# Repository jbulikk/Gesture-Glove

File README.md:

# Gesture Glove
The purpose of this project is to design and implement a prototype glove for gesture-based computer control, equipped with a set of sensors and a microcontroller. 

The project integrates flex sensors that measure finger bending and an inertial module containing an accelerometer and gyroscope, enabling gesture recognition based on spatial orientation. A key system component is the decision unit, which analyses sensor data and compares it with predefined patterns. Recognized
gestures are then transmitted to the computer via a USB HID interface.

The designed PCB, measuring 47.5 mm by 54.5 mm, was created to optimize the system's dimensions and facilitate durable mounting on the glove.
The results include successful recognition gestures and seamless
integration with the computer via USB HID. 

Future development plans involve further PCB miniaturization using a dedicated integrated circuit, the introduction of a wireless communication interface, and the design of a battery-powered system. Additionally, optimization of the decision algorithm is planned to improve gesture recognition accuracy.

# Overview

🎥 [Demo 1](https://youtube.com/shorts/HhJ9UxrMhsA?si=5mQ5Ls-5uZ076j6t)
🎥 [Demo 2](https://youtube.com/shorts/HhJ9UxrMhsA?si=OoEMOWHLwrecI-b9)

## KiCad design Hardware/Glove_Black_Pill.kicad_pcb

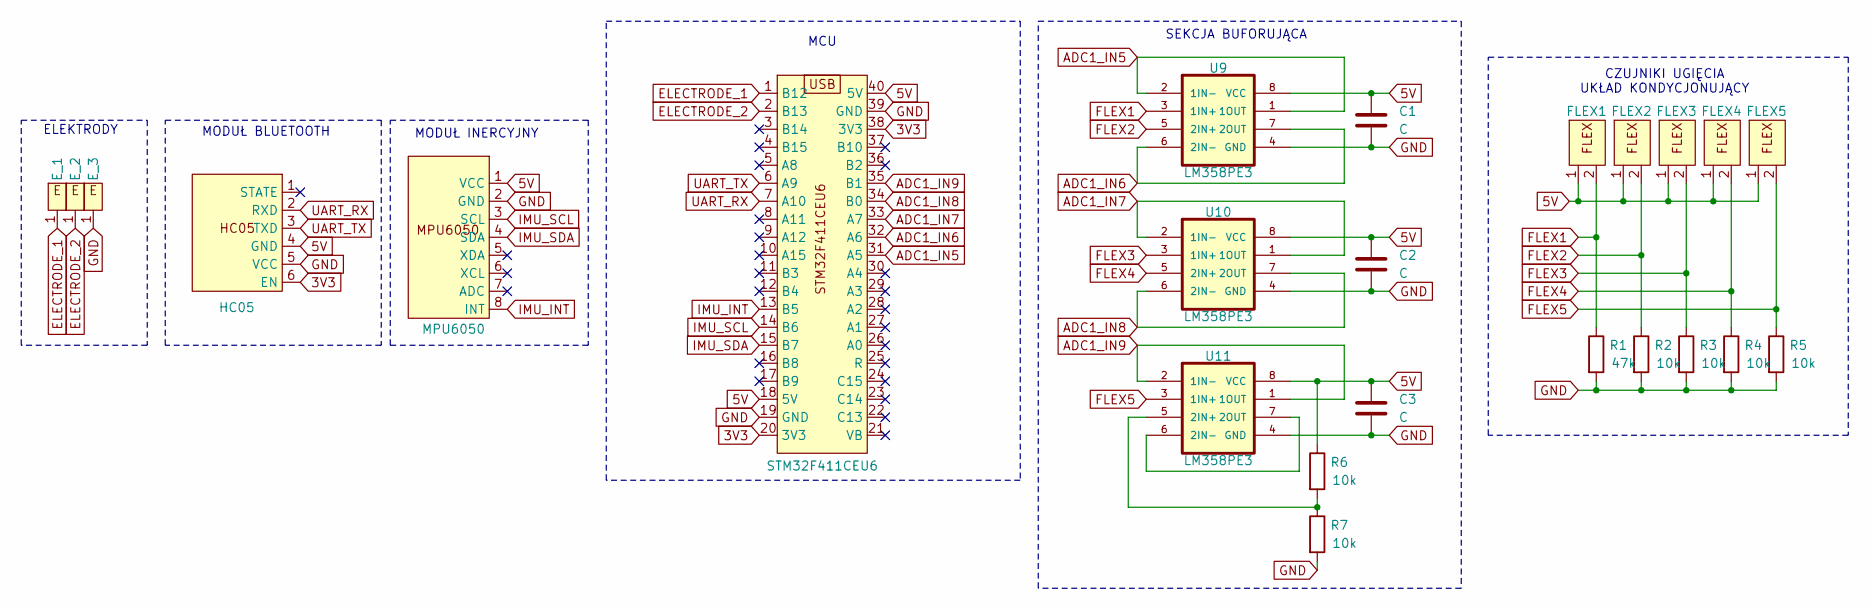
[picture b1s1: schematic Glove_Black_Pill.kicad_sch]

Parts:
C1, C2, C3: C; R_0805_2012Metric_Pad1.20x1.40mm_HandSolder
E_1, E_2, E_3: TestPoint_Loop_D2.50mm_Drill1.0mm
FLEX1, FLEX2, FLEX3, FLEX4, FLEX5: FLEX
HC05: HC-05
MPU6050: MPU6050
R1: 47k; R_0805_2012Metric_Pad1.20x1.40mm_HandSolder
R2, R3, R4, R5, R6, R7: 10k; R_0805_2012Metric_Pad1.20x1.40mm_HandSolder
STM32F411CEU6: STM32F411CEU6
U9, U10, U11: LM358PE3; DIP794W45P254L959H508Q8

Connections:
3V3: HC05.6 (EN), STM32F411CEU6.20 (3V3), STM32F411CEU6.38 (3V3)
5V: C1.1, C2.1, C3.1, FLEX1.1, FLEX2.1, FLEX3.1, FLEX4.1, FLEX5.1, HC05.4 (GND), MPU6050.1 (VCC), R6.1, STM32F411CEU6.18 (5V), STM32F411CEU6.40 (5V), U9.8 (VCC), U10.8 (VCC), U11.8 (VCC); also elsewhere on the board
ADC1_IN5: STM32F411CEU6.31 (A5), U9.1 (1OUT), U9.2 (1IN-)
ADC1_IN6: STM32F411CEU6.32 (A6), U9.6 (2IN-), U9.7 (2OUT)
ADC1_IN7: STM32F411CEU6.33 (A7), U10.1 (1OUT), U10.2 (1IN-)
ADC1_IN8: STM32F411CEU6.34 (B0), U10.6 (2IN-), U10.7 (2OUT)
ADC1_IN9: STM32F411CEU6.35 (B1), U11.1 (1OUT), U11.2 (1IN-)
ELECTRODE_1: E_1.1, STM32F411CEU6.1 (B12)
ELECTRODE_2: E_2.1, STM32F411CEU6.2 (B13)
FLEX1: FLEX1.2, R1.1, U9.3 (1IN+); also elsewhere on the board
FLEX2: FLEX2.2, R2.1, U9.5 (2IN+)
FLEX3: FLEX3.2, R3.1, U10.3 (1IN+)
FLEX4: FLEX4.2, R4.1, U10.5 (2IN+)
FLEX5: FLEX5.2, R5.1, U11.3 (1IN+)
GND: C1.2, C2.2, C3.2, E_3.1, HC05.5 (VCC), MPU6050.2 (GND), R1.2, R2.2, R3.2, R4.2, R5.2, R7.2, STM32F411CEU6.19 (GND), STM32F411CEU6.39 (GND), U9.4 (GND), U10.4 (GND), U11.4 (GND)
IMU_INT: MPU6050.8 (INT), STM32F411CEU6.13 (B5)
IMU_SCL: MPU6050.3 (SCL), STM32F411CEU6.14 (B6)
IMU_SDA: MPU6050.4 (SDA), STM32F411CEU6.15 (B7)
unnamed: R6.2, R7.1, U11.5 (2IN+)
unnamed: U11.6 (2IN-), U11.7 (2OUT)
UART_RX: HC05.2 (RXD), STM32F411CEU6.7 (A10)
UART_TX: HC05.3 (TXD), STM32F411CEU6.6 (A9)

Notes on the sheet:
MODUŁ BLUETOOTH
MODUŁ INERCYJNY
SEKCJA BUFORUJĄCA
ELEKTRODY
MCU
CZUJNIKI UGIĘCIA UKŁAD KONDYCJONUJĄCY

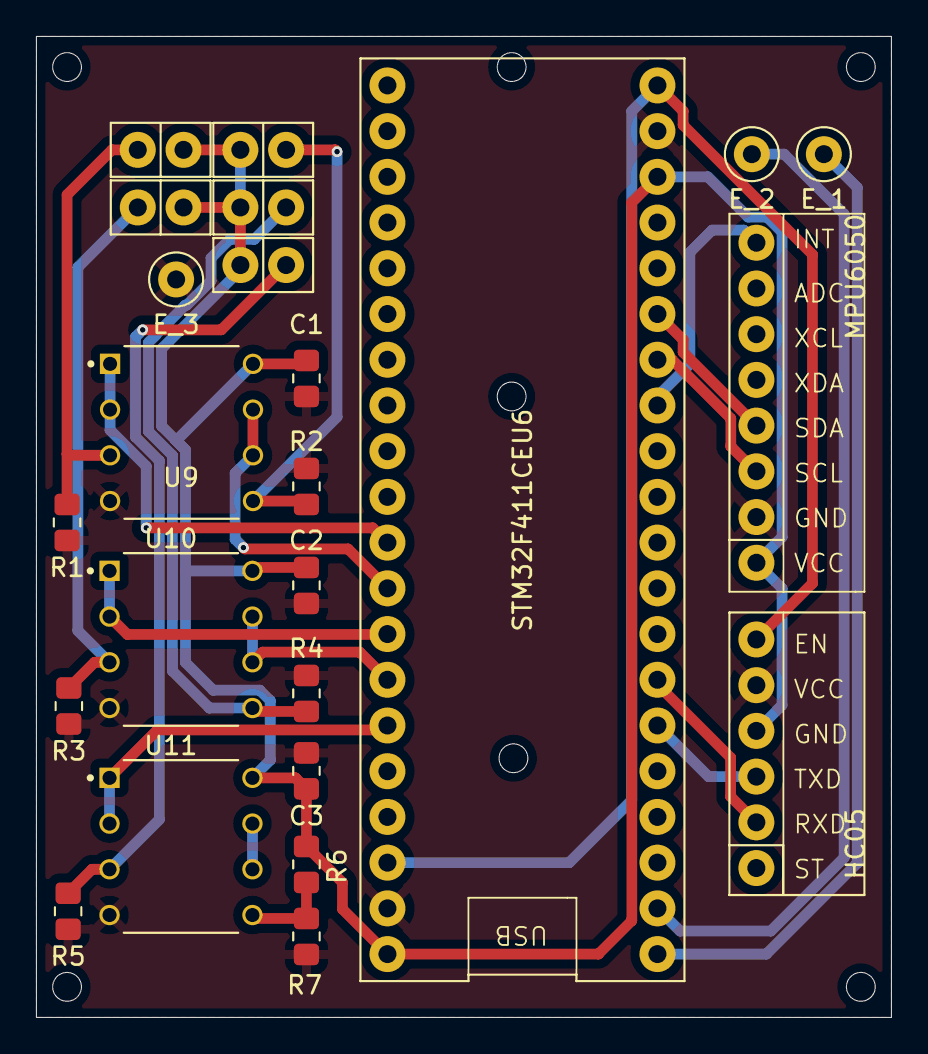
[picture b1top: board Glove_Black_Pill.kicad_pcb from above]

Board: 4 copper layers, 47.5 x 54.5 mm, 24 parts (0 on the bottom side), 22 nets.

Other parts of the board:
.: FLEX

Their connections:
5V: ..1; also elsewhere on the board
FLEX1: ..2; also elsewhere on the board

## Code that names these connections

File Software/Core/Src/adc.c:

/* USER CODE BEGIN Header */
/**
  ******************************************************************************
  * @file    adc.c
  * @brief   This file provides code for the configuration
  *          of the ADC instances.
  ******************************************************************************
  * @attention
  *
  * Copyright (c) 2024 STMicroelectronics.
  * All rights reserved.
  *
  * This software is licensed under terms that can be found in the LICENSE file
  * in the root directory of this software component.
  * If no LICENSE file comes with this software, it is provided AS-IS.
  *
  ******************************************************************************
  */
/* USER CODE END Header */
/* Includes ------------------------------------------------------------------*/
#include "adc.h"

/* USER CODE BEGIN 0 */

/* USER CODE END 0 */

ADC_HandleTypeDef hadc1;
DMA_HandleTypeDef hdma_adc1;

/* ADC1 init function */
void MX_ADC1_Init(void)
{

  /* USER CODE BEGIN ADC1_Init 0 */

  /* USER CODE END ADC1_Init 0 */

  ADC_ChannelConfTypeDef sConfig = {0};

  /* USER CODE BEGIN ADC1_Init 1 */

  /* USER CODE END ADC1_Init 1 */

  /** Configure the global features of the ADC (Clock, Resolution, Data Alignment and number of conversion)
  */
  hadc1.Instance = ADC1;
  hadc1.Init.ClockPrescaler = ADC_CLOCK_SYNC_PCLK_DIV2;
  hadc1.Init.Resolution = ADC_RESOLUTION_12B;
  hadc1.Init.ScanConvMode = ENABLE;
  hadc1.Init.ContinuousConvMode = ENABLE;
  hadc1.Init.DiscontinuousConvMode = DISABLE;
  hadc1.Init.ExternalTrigConvEdge = ADC_EXTERNALTRIGCONVEDGE_NONE;
  hadc1.Init.ExternalTrigConv = ADC_SOFTWARE_START;
  hadc1.Init.DataAlign = ADC_DATAALIGN_RIGHT;
  hadc1.Init.NbrOfConversion = 7;
  hadc1.Init.DMAContinuousRequests = ENABLE;
  hadc1.Init.EOCSelection = ADC_EOC_SEQ_CONV;
  if (HAL_ADC_Init(&hadc1) != HAL_OK)
  {
    Error_Handler();
  }

  /** Configure for the selected ADC regular channel its corresponding rank in the sequencer and its sample time.
  */
  sConfig.Channel = ADC_CHANNEL_9;
  sConfig.Rank = 1;
  sConfig.SamplingTime = ADC_SAMPLETIME_144CYCLES;
  if (HAL_ADC_ConfigChannel(&hadc1, &sConfig) != HAL_OK)
  {
    Error_Handler();
  }

  /** Configure for the selected ADC regular channel its corresponding rank in the sequencer and its sample time.
  */
  sConfig.Channel = ADC_CHANNEL_8;
  sConfig.Rank = 2;
  if (HAL_ADC_ConfigChannel(&hadc1, &sConfig) != HAL_OK)
  {
    Error_Handler();
  }

  /** Configure for the selected ADC regular channel its corresponding rank in the sequencer and its sample time.
  */
  sConfig.Channel = ADC_CHANNEL_7;
  sConfig.Rank = 3;
  if (HAL_ADC_ConfigChannel(&hadc1, &sConfig) != HAL_OK)
  {
    Error_Handler();
  }

  /** Configure for the selected ADC regular channel its corresponding rank in the sequencer and its sample time.
  */
  sConfig.Channel = ADC_CHANNEL_6;
  sConfig.Rank = 4;
  if (HAL_ADC_ConfigChannel(&hadc1, &sConfig) != HAL_OK)
  {
    Error_Handler();
  }

  /** Configure for the selected ADC regular channel its corresponding rank in the sequencer and its sample time.
  */
  sConfig.Channel = ADC_CHANNEL_5;
  sConfig.Rank = 5;
  if (HAL_ADC_ConfigChannel(&hadc1, &sConfig) != HAL_OK)
  {
    Error_Handler();
  }

  /** Configure for the selected ADC regular channel its corresponding rank in the sequencer and its sample time.
  */
  sConfig.Rank = 6;
  if (HAL_ADC_ConfigChannel(&hadc1, &sConfig) != HAL_OK)
  {
    Error_Handler();
  }

  /** Configure for the selected ADC regular channel its corresponding rank in the sequencer and its sample time.
  */
  sConfig.Rank = 7;
  if (HAL_ADC_ConfigChannel(&hadc1, &sConfig) != HAL_OK)
  {
    Error_Handler();
  }
  /* USER CODE BEGIN ADC1_Init 2 */

  /* USER CODE END ADC1_Init 2 */

}

void HAL_ADC_MspInit(ADC_HandleTypeDef* adcHandle)
{

  GPIO_InitTypeDef GPIO_InitStruct = {0};
  if(adcHandle->Instance==ADC1)
  {
  /* USER CODE BEGIN ADC1_MspInit 0 */

  /* USER CODE END ADC1_MspInit 0 */
    /* ADC1 clock enable */
    __HAL_RCC_ADC1_CLK_ENABLE();

    __HAL_RCC_GPIOA_CLK_ENABLE();
    __HAL_RCC_GPIOB_CLK_ENABLE();
    /**ADC1 GPIO Configuration
    PA5     ------> ADC1_IN5
    PA6     ------> ADC1_IN6
    PA7     ------> ADC1_IN7
    PB0     ------> ADC1_IN8
    PB1     ------> ADC1_IN9
    */
    GPIO_InitStruct.Pin = GPIO_PIN_5|GPIO_PIN_6|GPIO_PIN_7;
    GPIO_InitStruct.Mode = GPIO_MODE_ANALOG;
    GPIO_InitStruct.Pull = GPIO_NOPULL;
    HAL_GPIO_Init(GPIOA, &GPIO_InitStruct);

    GPIO_InitStruct.Pin = GPIO_PIN_0|GPIO_PIN_1;
    GPIO_InitStruct.Mode = GPIO_MODE_ANALOG;
    GPIO_InitStruct.Pull = GPIO_NOPULL;
    HAL_GPIO_Init(GPIOB, &GPIO_InitStruct);

    /* ADC1 DMA Init */
    /* ADC1 Init */
    hdma_adc1.Instance = DMA2_Stream0;
    hdma_adc1.Init.Channel = DMA_CHANNEL_0;
    hdma_adc1.Init.Direction = DMA_PERIPH_TO_MEMORY;
    hdma_adc1.Init.PeriphInc = DMA_PINC_DISABLE;
    hdma_adc1.Init.MemInc = DMA_MINC_ENABLE;
    hdma_adc1.Init.PeriphDataAlignment = DMA_PDATAALIGN_HALFWORD;
    hdma_adc1.Init.MemDataAlignment = DMA_MDATAALIGN_HALFWORD;
    hdma_adc1.Init.Mode = DMA_CIRCULAR;
    hdma_adc1.Init.Priority = DMA_PRIORITY_LOW;
    hdma_adc1.Init.FIFOMode = DMA_FIFOMODE_DISABLE;
    if (HAL_DMA_Init(&hdma_adc1) != HAL_OK)
    {
      Error_Handler();
    }

    __HAL_LINKDMA(adcHandle,DMA_Handle,hdma_adc1);

    /* ADC1 interrupt Init */
    HAL_NVIC_SetPriority(ADC_IRQn, 0, 0);
    HAL_NVIC_EnableIRQ(ADC_IRQn);
  /* USER CODE BEGIN ADC1_MspInit 1 */

  /* USER CODE END ADC1_MspInit 1 */
  }
}

void HAL_ADC_MspDeInit(ADC_HandleTypeDef* adcHandle)
{

  if(adcHandle->Instance==ADC1)
  {
  /* USER CODE BEGIN ADC1_MspDeInit 0 */

  /* USER CODE END ADC1_MspDeInit 0 */
    /* Peripheral clock disable */
    __HAL_RCC_ADC1_CLK_DISABLE();

    /**ADC1 GPIO Configuration
    PA5     ------> ADC1_IN5
    PA6     ------> ADC1_IN6
    PA7     ------> ADC1_IN7
    PB0     ------> ADC1_IN8
    PB1     ------> ADC1_IN9
    */
    HAL_GPIO_DeInit(GPIOA, GPIO_PIN_5|GPIO_PIN_6|GPIO_PIN_7);

    HAL_GPIO_DeInit(GPIOB, GPIO_PIN_0|GPIO_PIN_1);

    /* ADC1 DMA DeInit */
    HAL_DMA_DeInit(adcHandle->DMA_Handle);

    /* ADC1 interrupt Deinit */
    HAL_NVIC_DisableIRQ(ADC_IRQn);
  /* USER CODE BEGIN ADC1_MspDeInit 1 */

  /* USER CODE END ADC1_MspDeInit 1 */
  }
}

/* USER CODE BEGIN 1 */

/* USER CODE END 1 */

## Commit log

2024-12-02 addition of a decision-making unit
2024-12-02 Adding interrupts on both edges on pins 12 and 13
2024-12-03 good working debouncing
2024-12-20 changed fingers order due to pcb
2024-12-22 Change in the operation of the decision-making unit, checking the initial values of adc, changed low pass filter and alpha value
2025-01-07 decision unit checks every finger, flag and assign fingers values after all conversions
2025-01-07 decision unit checks every figer, EOC flag assign
2025-01-07 adding pitch calculations
2025-01-07 Handling of electrodes, limitation of gesture recognition
2025-01-08 adding gestures, code cleaning
2025-07-13 adding gitignore
2025-07-13 Remove Debug, .metadata, .settings folders from repo
2025-07-13 project restructure, adding hardware
